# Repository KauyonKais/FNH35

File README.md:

PCB deemed to be unsolderable by hand for me. As the corne keyboard suits my needs for a 35/36 key board, this project is on hold

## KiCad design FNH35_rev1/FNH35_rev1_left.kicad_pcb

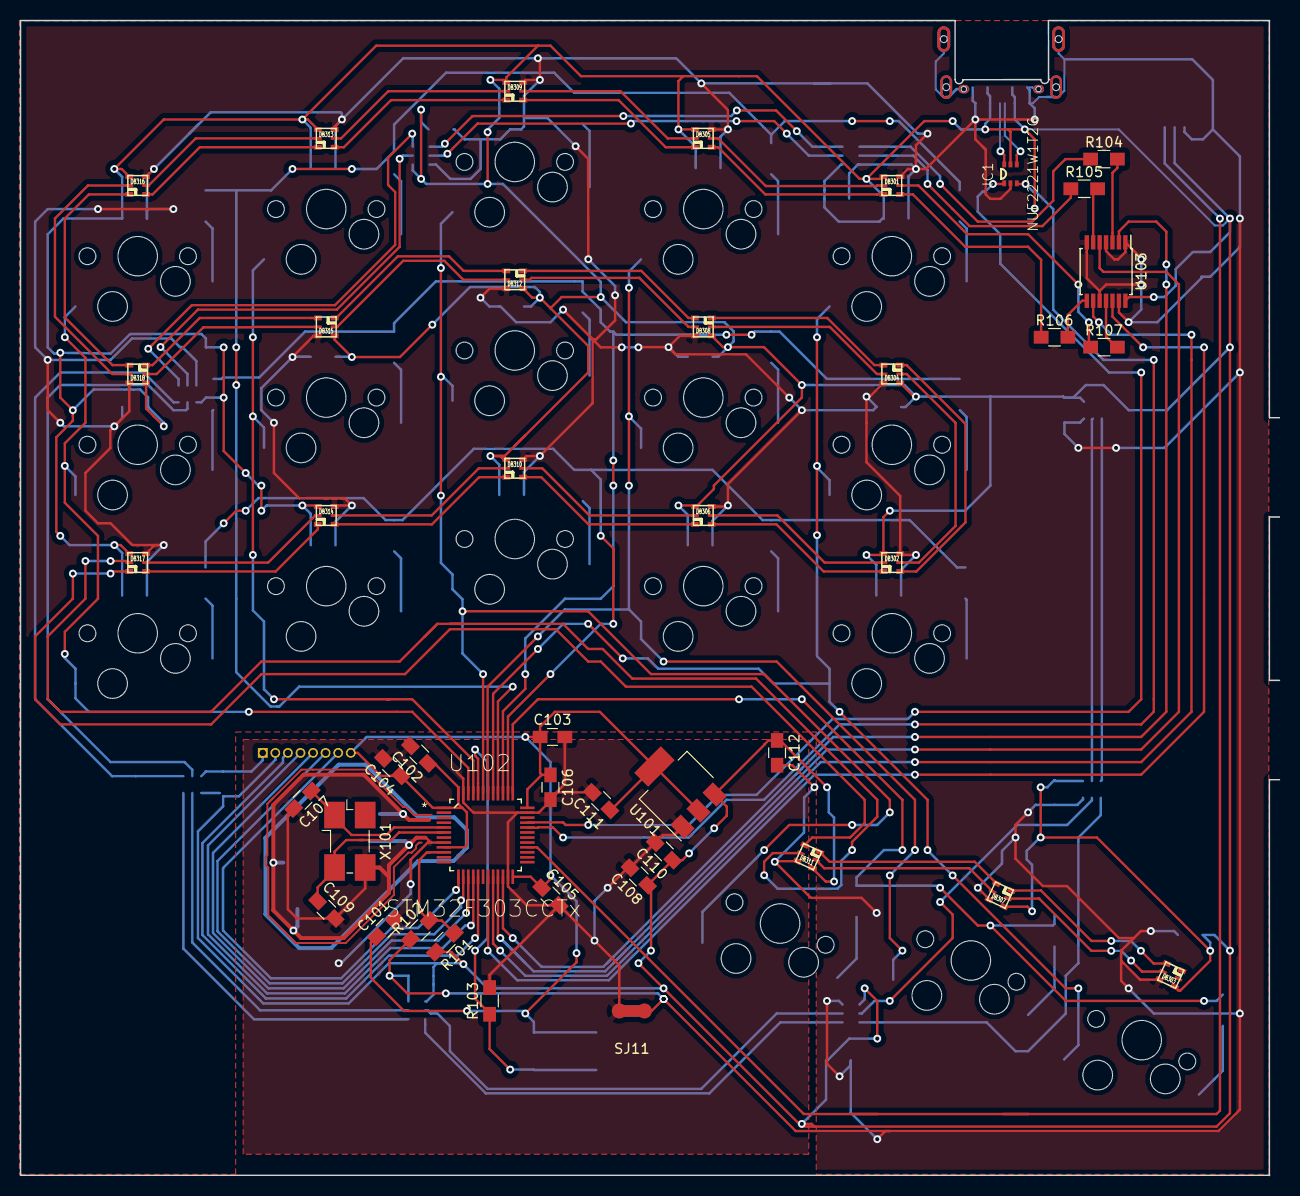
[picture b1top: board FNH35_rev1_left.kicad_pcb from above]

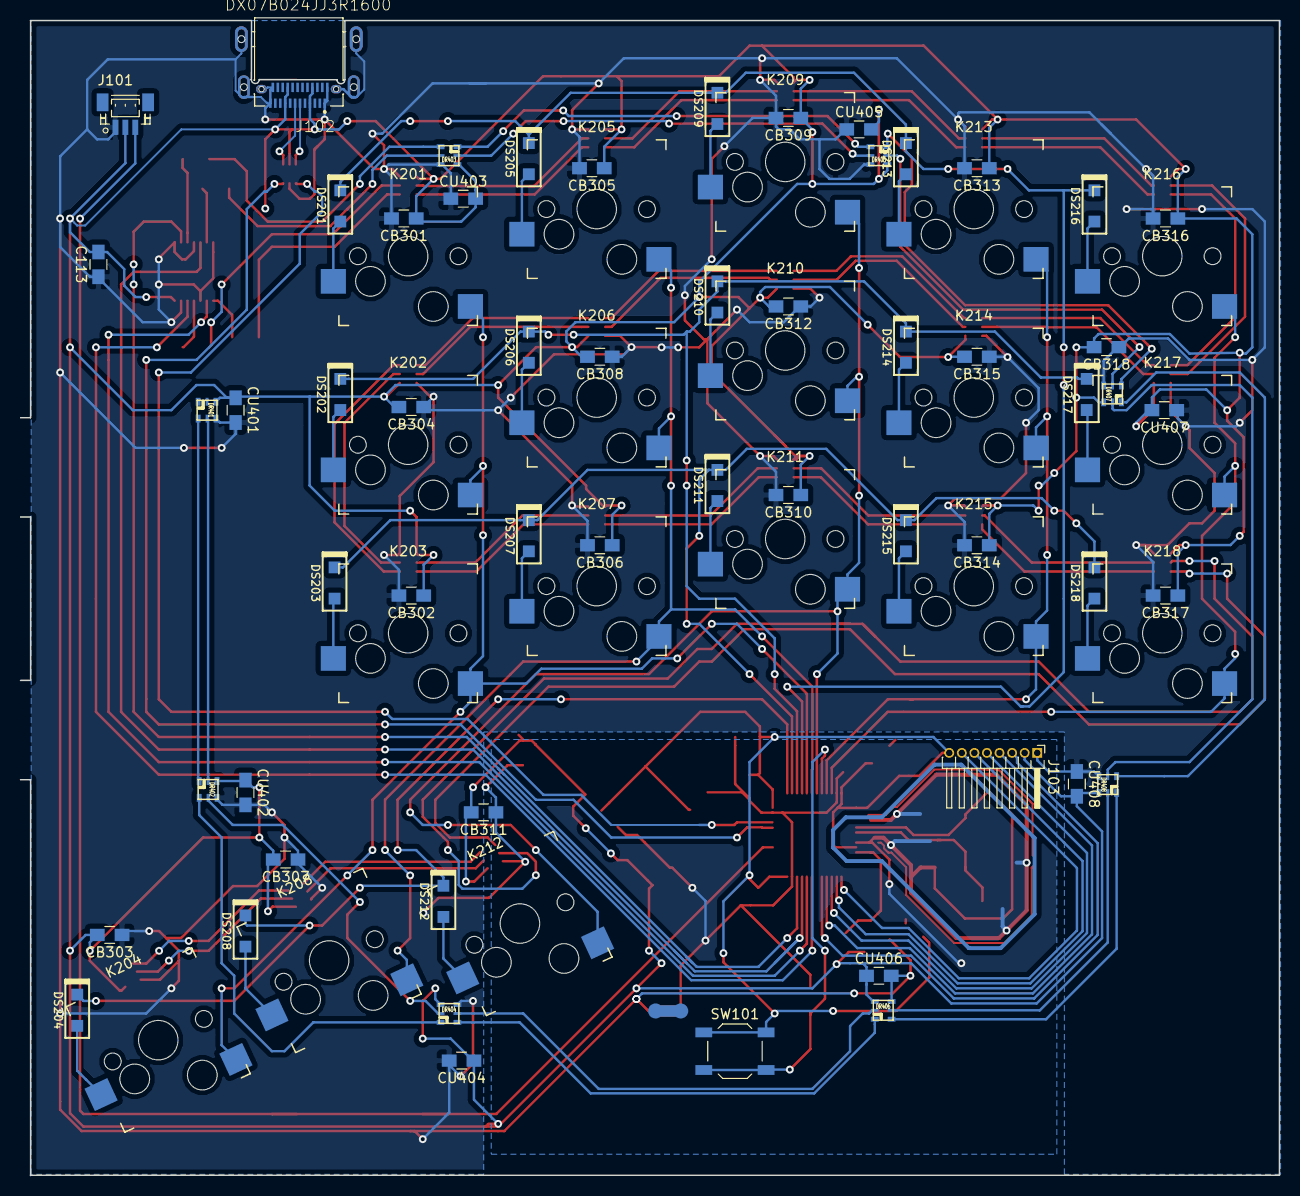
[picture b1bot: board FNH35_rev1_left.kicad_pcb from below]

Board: 2 copper layers, 127.2 x 116.7 mm, 118 parts (57 on the bottom side), 105 nets.

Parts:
C101: 4.7u; C_0805_HandSoldering
C102, C103, C104, C105, C113: 0.1u; C_0805_HandSoldering
C106: 1u; C_0805_HandSoldering
C107, C109: 33pf; C_0805_HandSoldering
C108, C111, C112: 10u; C_0805_HandSoldering
C110: 100n; C_0805_HandSoldering
CB301, CB302, CB303, CB304, CB305, CB306, CB307, CB308, CB309, CB310, CB311, CB312, CB313, CB314, CB315, CB316, CB317, CB318: 0.1u; C_0805_HandSoldering
CU401, CU402, CU403, CU404, CU405, CU406, CU407, CU408: 0.1u; C_0805_HandSoldering
DB301, DB302, DB303, DB304, DB305, DB306, DB307, DB308, DB309, DB310, DB311, DB312, DB313, DB314, DB315, DB316, DB317, DB318: APA102; APA102-2020
DR401, DR402, DR403, DR404, DR405, DR406, DR407, DR408: APA102; APA102-2020
DS201, DS202, DS203, DS204, DS205, DS206, DS207, DS208, DS209, DS210, DS211, DS212, DS213, DS214, DS215, DS216, DS217, DS218: D; D_SOD123_hand
IC1: NUF2221W1T2G; SOT-363
J101: Conn_01x03; JST_SH_BM03B-SRSS-TB_03x1.00mm_Straight
J102: DX07B024JJ3R1600; JAE_DX07B024JJ3R1600
J103: Conn_01x08; Pin_Header_Angled_1x08_Pitch1.27mm
K201, K202, K203, K204, K205, K206, K207, K208, K209, K210, K211, K212, K213, K214, K215, K216, K217, K218: KEYSW; Kailh_socket
R101: 4k1; R_0805_HandSoldering
R102: 9k1; R_0805_HandSoldering
R103: 10kR; R_0805_HandSoldering
R104, R105, R106, R107: 300; R_0805_HandSoldering
SJ11: SOLDER_JUMPER; gndcm
SW101: SW_PUSH; SW_SPST_TL3342
U101: LD1117S33TR_SOT223; SOT-223-3_TabPin2
U102: STM32F303CCTx; QFP50P900X900X160-48N
U103: 74AHCT125; TSSOP-14_4.4x5mm_Pitch0.65mm
X101: XTAL_GND; Crystal_SMD_0603-4pin_6.0x3.5mm_HandSoldering

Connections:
+3V3: C101.1, C102.1, C103.1, C104.1, C105.1, C106.1, C111.1, J103.8, SW101.1, U101.2, U102.1, U102.9, U102.24, U102.36, U102.48
+5V: C108.1, C110.1, C112.1, C113.2, CB301.1, CB302.1, CB303.2, CB304.2, CB305.1, CB306.1, CB307.2, CB308.2, CB309.1, CB310.1, CB311.2, CB312.2, CB313.1, CB314.1, CB315.2, CB316.1, CB317.1, CB318.2, CU401.1, CU402.1, CU403.2, CU404.1, CU405.2, CU406.1, CU407.2, CU408.2, DB301.5, DB302.5, DB303.5, DB304.5, DB305.5, DB306.5, DB307.5, DB308.5, DB309.5, DB310.5, DB311.5, DB312.5, DB313.5, DB314.5, DB315.5, DB316.5, DB317.5, DB318.5, DR401.5, DR402.5, DR403.5, DR404.5, DR405.5, DR406.5, DR407.5, DR408.5, IC1.5, J101.2, J102.A4, J102.A9, J102.B4, J102.B9, J103.2, R101.2, U101.3, U103.14
/LADC: R101.1, R102.2, U102.10
/LBOOT: R103.1, SW101.2, U102.44
/LCKI_Back: U102.19, U103.12
/LCKI_Und: U102.21, U103.5
/LDA+: IC1.6, J102.A6
/LDA-: IC1.4, J102.A7
/LEDMatrix_Underglow/CKI: DR403.3, R105.1
/LEDMatrix_Underglow/SDI: DR403.2, R104.1
/LEDMatrix_perKey/CKI: DB301.3, R107.1
/LEDMatrix_perKey/SDI: DB301.2, R106.1
/LPA13: J103.7, U102.13
/LPA14: J103.6, U102.14
/LPA15: J103.5, U102.15
/LPA16: J103.4, U102.16
/LPA17: J103.3, U102.17
/LSDI_Back: U102.20, U103.9
/LSDI_Und: U102.22, U103.2
/LSerConn: J101.3, U102.28
/LUSB+: IC1.1, U102.33
/LUSB-: IC1.3, U102.32
/Lcol0: K216.1, K217.1, K218.1, U102.46
/Lcol1: K213.1, K214.1, K215.1, U102.45
/Lcol2: K209.1, K210.1, K211.1, K212.1, U102.43
/Lcol3: K205.1, K206.1, K207.1, K208.1, U102.42
/Lcol4: K201.1, K202.1, K203.1, K204.1, U102.41
/Lrow0: DS201.1, DS205.1, DS209.1, DS213.1, DS216.1, U102.40
/Lrow1: DS202.1, DS206.1, DS210.1, DS214.1, DS217.1, U102.39
/Lrow2: DS203.1, DS207.1, DS211.1, DS215.1, DS218.1, U102.38
/Lrow3: DS204.1, DS208.1, DS212.1, U102.37
GND: C112.2, C113.1, CB301.2, CB302.2, CB303.1, CB304.1, CB305.2, CB306.2, CB307.1, CB308.1, CB309.2, CB310.2, CB311.1, CB312.1, CB313.2, CB314.2, CB315.1, CB316.2, CB317.2, CB318.1, CU401.2, CU402.2, CU403.1, CU404.2, CU405.1, CU406.2, CU407.1, CU408.1, DB301.4, DB302.4, DB303.4, DB304.4, DB305.4, DB306.4, DB307.4, DB308.4, DB309.4, DB310.4, DB311.4, DB312.4, DB313.4, DB314.4, DB315.4, DB316.4, DB317.4, DB318.4, DR401.4, DR402.4, DR403.4, DR404.4, DR405.4, DR406.4, DR407.4, DR408.4, IC1.2, J101.1, J102.A1, J102.A12, J102.B1, J102.B12, J102.S1, J102.S2, J102.S3, J102.S4, J102.S5, J102.S6, J103.1, R102.1, SJ11.2, U103.1, U103.4, U103.7, U103.10, U103.13
GNDD: C101.2, C102.2, C103.2, C104.2, C105.2, C106.2, C107.2, C108.2, C109.2, C110.2, C111.2, R103.2, SJ11.1, U101.1, U102.8, U102.23, U102.35, U102.47, X101.3
unnamed: C107.1, U102.5, X101.1
unnamed: C109.1, U102.6, X101.2
unnamed: DB301.1, DB305.2
unnamed: DB301.6, DB305.3
unnamed: DB302.1, DB306.2
unnamed: DB302.2, DB304.1
unnamed: DB302.3, DB304.6
unnamed: DB302.6, DB306.3
unnamed: DB303.2, DB307.1
unnamed: DB303.3, DB307.6
unnamed: DB304.2, DB308.1
unnamed: DB304.3, DB308.6
unnamed: DB305.1, DB309.2
unnamed: DB305.6, DB309.3
unnamed: DB306.1, DB310.2
unnamed: DB306.6, DB310.3
unnamed: DB307.2, DB311.1
unnamed: DB307.3, DB311.6
unnamed: DB308.2, DB312.1
unnamed: DB308.3, DB312.6
unnamed: DB309.1, DB313.2
unnamed: DB309.6, DB313.3
unnamed: DB310.1, DB314.2
unnamed: DB310.6, DB314.3
unnamed: DB311.2, DB317.1
unnamed: DB311.3, DB317.6
unnamed: DB312.2, DB315.1
unnamed: DB312.3, DB315.6
unnamed: DB313.1, DB316.2
unnamed: DB313.6, DB316.3
unnamed: DB314.1, DB317.2
unnamed: DB314.6, DB317.3
unnamed: DB315.2, DB318.1
unnamed: DB315.3, DB318.6
unnamed: DB316.1, DB318.2
unnamed: DB316.6, DB318.3
unnamed: DR401.2, DR402.1
unnamed: DR401.3, DR402.6
unnamed: DR402.2, DR404.1
unnamed: DR402.3, DR404.6
unnamed: DR403.1, DR405.2
unnamed: DR403.6, DR405.3
unnamed: DR404.2, DR406.1
unnamed: DR404.3, DR406.6
unnamed: DR405.1, DR407.2
unnamed: DR405.6, DR407.3
unnamed: DR406.2, DR408.1
unnamed: DR406.3, DR408.6
unnamed: DR407.1, DR408.2
unnamed: DR407.6, DR408.3
unnamed: DS201.2, K201.2
unnamed: DS202.2, K202.2
unnamed: DS203.2, K203.2
unnamed: DS204.2, K204.2
unnamed: DS205.2, K205.2
unnamed: DS206.2, K206.2
unnamed: DS207.2, K207.2
unnamed: DS208.2, K208.2
unnamed: DS209.2, K209.2
unnamed: DS210.2, K210.2
unnamed: DS211.2, K211.2
unnamed: DS212.2, K212.2
unnamed: DS213.2, K213.2
unnamed: DS214.2, K214.2
unnamed: DS215.2, K215.2
unnamed: DS216.2, K216.2
unnamed: DS217.2, K217.2
unnamed: DS218.2, K218.2
unnamed: R104.2, U103.3
unnamed: R105.2, U103.6
unnamed: R106.2, U103.8
unnamed: R107.2, U103.11

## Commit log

2018-08-28 first footprint lib
2018-08-30 empty kicad project
2018-09-01 Switch Matrix added
2018-09-04 added new LED sheet using APA102 2020s
2018-09-04 perKey and Underglow LEDs sheets done, begun USB. Need 5V upshift for data lines on APA102git add .
2018-09-05 added caps to LEDs
2018-09-05 Upshifter 3->5V wired up
2018-09-06 finished (?)
2018-09-06 started allocating footprints
2018-09-07 netlist generated, footprints allocated
2018-09-07 Switches and LEDs in place
2018-09-07 more pcb layouting, decided to get rid of fuse in next step
2018-09-08 almost done
2018-09-08 noticed the diodes are conflicting with the sockets, deleting traces from here
2018-09-08 routed backlight data
2018-09-08 pcb finished. Next up: review and left hand
2018-09-10 redoing wiring, deleted shitty stuff
2018-09-11 before mirror attempts
2018-09-12 mirrored PCB: success
2018-09-14 finished, again
2018-09-14 updated gerber files and left schematic pdf
2018-09-15 separated left half
2018-09-15 left half crystal reworked
2018-09-15 separated and rework crystal on right half
2018-09-16 GND and GNDD disconnected
2018-10-06 start of case design
2018-10-06 updated schematic pdfs
